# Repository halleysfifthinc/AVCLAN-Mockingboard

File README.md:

# AVCLAN Mockingboard

This project adds an aux in to the stock head unit of compatible Toyota vehicles by emulating an external CD changer. The Mockingboard communicates with the head unit over the AVC-LAN bus, Toyota's name for their messaging protocol over the NEC (now Renesas) IEBus. Also included is a Wireshark dissector for IEBus and AVC-LAN. AVC-LAN is sparsely documented publicly; this dissector collects what's known from prior art alongside my own findings.

# Features:

- Select/switch between internal CD player and mockingboard by pressing the "CD" button (repeated presses toggle between internal and external CD players)
- Generally complete handling of physical interface (track next/prev, fast-forward/rewind, track/disk repeat and random; "scan" button and change disc buttons are currently unimplemented for lack of use/purpose)
- Play/pause, next/prev control of connected phones via headset functions (mimicing the button press on a wired headset; requires phone support and connection using a TRRS aux cable)

## Future plans (Mockingboard v2)

- Bluetooth functionality
  - "Scan" button repurposed to enter bluetooth pairing mode
  - Button actions (play/pause, track skip, ff/rw, \[disc\] repeat/shuffle) mapped to AVRCP
  - Song info/status (time, etc) relayed to head-unit (i.e. time display matches actual song/audio time)
- Redesigned hardware based on RPi Pico 2W (RP2350 + Bluetooth)
  - PIO used to implement:
    - AVCLAN comms
    - I2S audio
  - Dual audio input options (aux in, bluetooth)
    - Switched audio jack to sense aux plug presence
  - Audio codec with differential output (better rejection of electrical noise, e.g. from adjacent AVCLAN bus lines)
  - Switching regulator (easier assembly)
  - CAN transceiver
    - TX/RX connected to different diodes (or different pads of a single dual/multicolor LED package) for observability

# Helpful links/prior art:

- IEBus/AVCLAN decoder and message dumps (inc. a CD changer) for Sigrok
    - https://github.com/sigrokproject/sigrok-test/pull/22
    - https://github.com/sigrokproject/sigrok-dumps/pull/43
    - https://github.com/sigrokproject/libsigrokdecode/pull/106
- https://web.archive.org/web/20230319000356/http://softservice.com.pl/corolla/avc/avclan.php
- https://web.archive.org/web/20040617005106/http://www.interfacebus.com/Design_Connector_IEbus.html
- https://web.archive.org/web/2/https://old.pinouts.ru/Car-Stereo-Toyota-Lexus/Toyota_1990-2002_CD_Chang_pinout.shtml
- https://web.archive.org/web/20240519043021/https://pop.fsck.pl/hardware/toyota-corolla.html
- https://github.com/GadgetNutt/AVC-LAN-Module-Builder

# Firmware

### Building

#### With VS Code:

1. Install VS Code and Docker
    - Required extensions: Dev Containers
2. Open repo in VS code and wait for notification asking to re-open in dev container.
    - Wait for container to build and extensions to install
3. Select CMake build configuration
4. Start developing!

#### Natively/without VS Code Dev Containers
1. Install avr-gcc >= v13.1, binutils >= v2.39, cmake >= v3.24
2. Configure cmake with a hardware-target preset, `cmake --list-presets` to discover options
    - Trigger builds with e.g. `cmake --build out/build/attiny3216`
3. Start developing!

# Hardware

## First generation

See [here](hardware/mockingboard-v1/README.md) for details.

## Second generation

Under development!

# Protocol reverse-engineering

The "scripts/packet-analysis" folder contains a [Wireshark](https://www.wireshark.org/) [Lua plugin](https://www.wireshark.org/docs/wsdg_html_chunked/wsluarm.html) that defines a dissector for IEBUS and AVC-LAN messages.

The dissector's `known_devices` / `known_actions` tables are the source of truth
for AVC-LAN device and action names. `scripts/sync_avclan_enums.py` reconciles
the firmware's C++ `Device` / `Action` enums (and every reference under `src/`)
against them, matching by value so renamed values are propagated. It runs as a
pre-commit hook — the top-level CMake configure step points `core.hooksPath` at
`.githooks/`, so `cmake --preset …` activates it automatically (opt out with
`-DINSTALL_GIT_HOOKS=OFF`; `git commit --no-verify` bypasses one commit). The
hook only reports drift; run `scripts/sync_avclan_enums.py --fix` to apply, and
`--lint` to check that the dissector's own names are valid identifiers.

# License

The firmware for this project is licensed under the [GNU GPLv3](https://www.gnu.org/licenses/gpl-3.0.html). The AVR-Attiny3216 hardware target depends on a vendored [MIT](https://spdx.org/licenses/MIT) licensed [UART library](https://github.com/jnk0le/AVR-UART-lib), and the [MPL-2.0](https://www.mozilla.org/MPL/2.0/) licensed [avr-libstdcpp](https://github.com/modm-io/avr-libstdcpp/) C++ STL subset.
The hardware is licensed under the [Solderpad Hardware License v2.1](http://solderpad.org/licenses/SHL-2.1/), a
wraparound license to the [Apache License 2.0](https://apache.org/licenses/LICENSE-2.0.txt).

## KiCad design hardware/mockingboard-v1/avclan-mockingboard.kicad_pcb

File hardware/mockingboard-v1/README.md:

# Hardware

I ordered the boards partially assembled from JLCPCB (to keep costs down, I ordered and soldered some non-standard/stocked parts myself.)

The non-populated/assembled BOM is:

| Mouser #:           | Mfr. #:          | Desc.:                                                                                                       | Order Qty. | Unit Price (USD) |
| ------------------- | ---------------- | ------------------------------------------------------------------------------------------------------------ | ---------- | ----------- |
| 579-ATTINY3216-SNR  | ATTINY3216-SNR   | 8-bit Microcontrollers - MCU 8-bit Microcontrollers - MCU 20MHz, 32KB, SOIC20, Ind 105C, Green, T&R          | 1          | $1.27       |
| 523-L717SDE09PA4CH4 | L717SDE09PA4CH4F | D-Sub Standard Connectors D-Sub Standard Connectors D SUB R/A                                                | 1          | $1.98       |
| 490-SJ-43514        | SJ-43514         | Phone Connectors Phone Connectors audio jack, 3.5 mm, rt, 4 conductor, through hole, 0 switches              | 1          | $1.35       |
| 667-ERZ-V20D220     | ERZ-V20D220      | Varistors Varistors 22V 2000A ZNR SUR ABSORBER 20MM                                                          | 1          | $1.24       |
| 538-22-28-8093      | 22-28-8093       | Headers & Wire Housings Headers & Wire Housings 2.54MM BREAKAWAY RA 9 CKT Gold                               | 2          | $0.76       |
| 865-XC6701D502JR-G  | XC6701D502JR-G   | LDO Voltage Regulators LDO Voltage Regulators 28V High Speed Voltage Regulator                               | 1          | $1.36       |
| 563-EXN-23350-BK    | EXN-23350-BK     | Enclosures, Boxes, & Cases Enclosures, Boxes, & Cases Extruded Aluminum Enclosure Black (1.4 X 2.7 X 1.9 In) | 1          | $14.40      |

An earlier version of the board* lacked cutouts in the corners to fit the ends of the intended housing, so I haven't used the listed enclosure (yet).

*Only version of the board I have ordered so far.

### Flashing

The CMake target `flash` uses the AVRDude utility using the "serialupdi" programmer type. I use a [USB => Serial converter](https://www.adafruit.com/product/5335) with the Rx and Tx lines connected, using one of the options described [by SpenceKonde here](https://github.com/SpenceKonde/AVR-Guidance/blob/master/UPDI/jtag2updi.md).

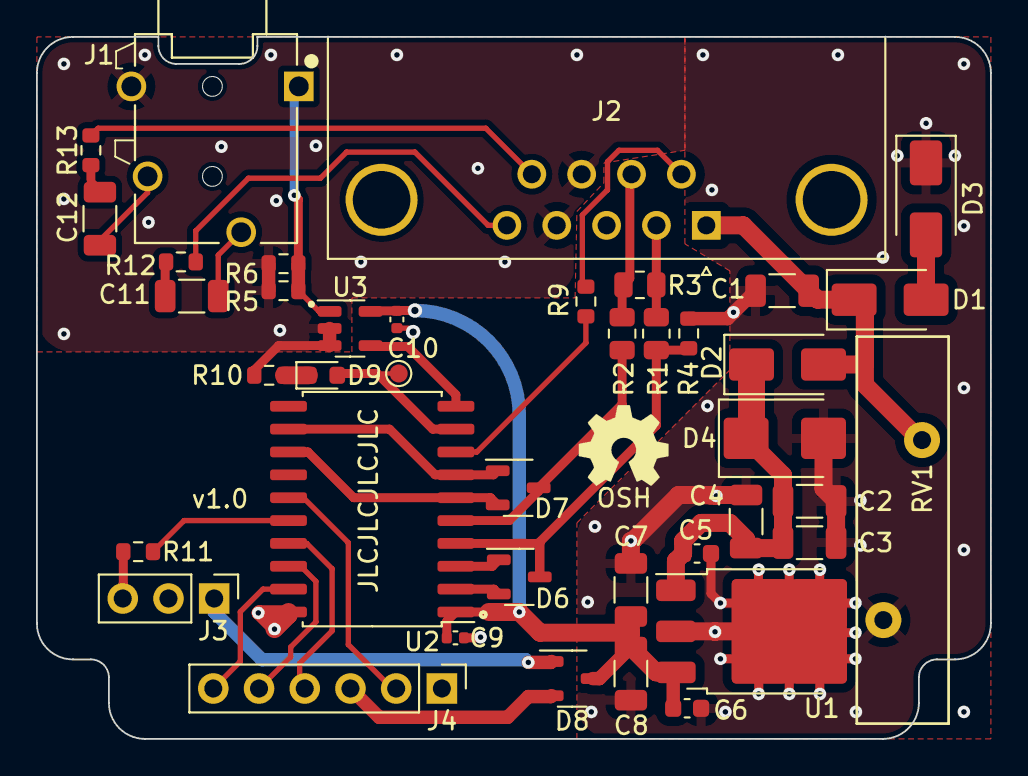
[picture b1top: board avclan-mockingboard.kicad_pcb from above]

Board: 4 copper layers, 53.0 x 39.0 mm, 40 parts (0 on the bottom side), 33 nets.

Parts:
C1: 1n 100V; C_1206_3216Metric
C2, C3, C4: 10u 50V; C_1206_3216Metric
C5, C6: 1u 50V; C_0603_1608Metric
C7, C8, C11, C12: 47u 10V; C_1206_3216Metric
C9, C10: 4u7; C_0402_1005Metric
D1, D2: SS210; D_SMA
D3: 1SMAF4742A; D_SMA
D4: SM6T15A; D_SMB
D6, D8: BAT54C,215; SOT-23-3
D7: BAT54A,215; SOT-23-3
D9: KT-0603R; LED_0603_1608Metric
J1: Audio In; CUI_SJ-43514
J2: DB9; DSUB-9_Male_Horizontal_P2.77x2.84mm_EdgePinOffset7.70mm_Hou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
J3: Conn_01x03; PinHeader_1x03_P2.54mm_Vertical
J4: Conn_01x06; PinHeader_1x06_P2.54mm_Vertical
R1, R2: 180; R_0805_2012Metric
R3: 120; R_0805_2012Metric
R4, R5, R6, R9: 10k; R_0603_1608Metric
R10, R11: 470; R_0603_1608Metric
R12, R13: 15; R_0603_1608Metric
RV1: ERZ-V20D220; RV_Disc_D21.5mm_W5.1mm_P10mm
TP1: TestPoint; TestPoint_Pad_D1.0mm
U1: XC6701D502JR-G; TO-252-3_TabPin2
U2: ATtiny3216; SOIC-20W_7.5x12.8mm_P1.27mm
U3: 74LVC1G66; SOT-23-5

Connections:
+5V: C6.1, C7.1, C8.1, C9.1, C10.1, D8.3 (K), U1.3 (Vout), U2.1 (VCC), U3.5 (VCC)
+12V: C1.1, D1.1 (K), D2.2 (A), J2.1 (BAT), RV1.1
/12V_CLEAN: C2.1, C3.1, C4.1, C5.1, D2.1 (K), D4.1 (A1), U1.1 (Vin)
/AC2 OUT: D9.2 (A), TP1.1, U2.9 (PB2)
/AUDIO-L: J2.9 (R-), R13.1
/AUDIO-R: J2.5 (GND), R12.2
AUDIO_L: C12.1, J1.2 (T)
AUDIO_R: C11.1, J1.3 (R1)
AVCLAN_BUS_TX+: J2.2 (BUS+), R1.2, R3.2
AVCLAN_BUS_TX-: J2.7 (BUS-), R2.2, R3.1
AVCLAN_TX+: D6.3 (A), R1.1, R4.1, U2.4 (PA6)
AVCLAN_TX-: D7.3 (A), R2.1, U2.5 (PA7)
CTS: J4.2, U2.15 (PC3)
GND: C1.2, C2.2, C3.2, C4.2, C5.2, C6.2, C7.2, C8.2, C9.2, C10.2, D3.1 (K), D4.2 (A2), J1.4 (R2), J2.3 (L+), J2.4 (R+), J2.8 (L-), J3.2, J4.1, R4.2, R5.2, R6.2, R10.2, RV1.2, U1.2 (GND), U2.20 (GND), U3.2, U3.3 (GND)
MIC_CONTROL: U2.10 (PB1), U3.4
MUTE: R9.1, U2.8 (PB3)
unnamed: C11.2, R12.1
unnamed: C12.2, R13.2
unnamed: D1.2 (A), D3.2 (A)
unnamed: D9.1 (K), R10.1
unnamed: J1.1 (S), R5.1, R6.1, U3.1
unnamed: J2.6 (IGN/ACC), R9.2
unnamed: J3.3, R11.2
RTS: J4.6, U2.19 (PA3)
RxD: J4.4, U2.18 (PA2)
SERIAL_PWR: D8.2 (K), J4.3
TxD: J4.5, U2.17 (PA1)
UPDI: R11.1, U2.16 (~RESET/PA0)
UPDI_PWR: D8.1 (A), J3.1
WOA: D6.2 (K), U2.2 (PA4)
WOB: D6.1 (K), U2.3 (PA5)
WOC: D7.1 (K), U2.7 (PB4), U2.12 (PC0)
WOD: D7.2 (K), U2.6 (PB5), U2.13 (PC1)

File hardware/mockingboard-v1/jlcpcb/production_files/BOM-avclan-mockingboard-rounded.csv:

Comment,Designator,Footprint,LCSC
SM6T15A,D4,D_SMB,C118275
"BAT54A,215",D7,SOT-23-3,C130910
10u 50V,"C2,C3,C4",C_1206_3216Metric,C13585
SS210,"D1,D2",D_SMA,C14996
1u 50V,"C5,C6",C_0603_1608Metric,C15849
10k,"R4,R5,R6,R7,R8,R9",R_0603_1608Metric,C17414
120,R3,R_0805_2012Metric,C17437
15,"R12,R13",R_0603_1608Metric,C22810
KT-0603R,D9,LED_0603_1608Metric,C2286
470,"R10,R11",R_0603_1608Metric,C23179
4u7,"C10,C9",C_0402_1005Metric,C23733
180,"R1,R2",R_0805_2012Metric,C25270
1SMAF4742A,D3,D_SMA,C3013762
"BAT54C,215","D6,D8",SOT-23-3,C37704
74LVC1G66,U3,SOT-23-5,C5375974
3V3,D10,D_MiniMELF,C8056
1n 100V,C1,C_1206_3216Metric,C9196
47u 10V,"C11,C12,C7,C8",C_1206_3216Metric,C96123

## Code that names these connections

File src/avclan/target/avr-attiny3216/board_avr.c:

// copyright (C) 2006 Marcin Slonicki <marcin@softservice.com.pl>
// copyright (C) 2007 Louis Frigon
// Copyright (C) 2015 Allen Hill <allenofthehills@gmail.com>
// SPDX-License-Identifier: GPL-3.0-or-later

// ATtiny3216 board bring-up: main-clock prescaler + GPIO config for pins not
// owned by a peripheral's own init.

#include <avr/interrupt.h>
#include <avr/io.h>
#include <avr/xmega.h> // _PROTECTED_WRITE

#include "hal/board.h"

void board_init(void) {
  // Main clock prescale (CLK_PRESCALE / CLK_PRESCALE_DIV come from the build).
  _PROTECTED_WRITE(CLKCTRL.MCLKCTRLB, (CLK_PRESCALE | CLK_PRESCALE_DIV));

  // Set pins PC2-3, PB0,3-5 as inputs
  PORTC.DIRCLR = (PIN2_bm | // Unconnected
                  PIN3_bm); // CTS
  PORTB.DIRCLR = (PIN0_bm | // Unconnected
                  PIN3_bm | // IGN_SENSE
                  PIN4_bm | // Unused, but connected to WOC (PC0)
                  PIN5_bm); // Unused, but connected to WOD (PC1)

  // Enable pull-up resistor and disable input buffer (reduces any EM caused
  // pin toggling and saves power) for unused and unconnected pins
  PORTC.PIN2CTRL = PORT_PULLUPEN_bm | PORT_ISC_INPUT_DISABLE_gc;
  PORTB.PIN0CTRL = PORT_PULLUPEN_bm | PORT_ISC_INPUT_DISABLE_gc;

  // TODO: Remove once IGN_SENSE hardware is fixed
  PORTB.DIRSET = PIN3_bm;
  PORTB.OUTSET = PIN3_bm;

  // Output only pins: PA3-5, PB1-2,4-5; PC0-1
  // TODO: TxD (PA1), RTS (PA3) is output only, test if RxD needs the input
  // buffer or if the UART peripheral bypasses it
  PORTA.PIN3CTRL = PORT_ISC_INPUT_DISABLE_gc; // RTS
  PORTA.PIN4CTRL = PORT_ISC_INPUT_DISABLE_gc; // WOA
  PORTA.PIN5CTRL = PORT_ISC_INPUT_DISABLE_gc; // WOB
  PORTB.PIN1CTRL = PORT_ISC_INPUT_DISABLE_gc; // MIC_CONTROL
  PORTB.PIN4CTRL = PORT_ISC_INPUT_DISABLE_gc; // non-driving WOC
  PORTB.PIN5CTRL = PORT_ISC_INPUT_DISABLE_gc; // non-driving WOD
  PORTC.PIN0CTRL = PORT_ISC_INPUT_DISABLE_gc; // WOC
  PORTC.PIN1CTRL = PORT_ISC_INPUT_DISABLE_gc; // WOD
}

void board_enable_interrupts(void) { sei(); }

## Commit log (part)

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2015-07-20 Branch update
2015-07-23 Merged Marcin's AVC-LAN driver
2015-07-23 Updated Makefile for new driver/main file
2015-07-24 Compile/linking required changes
2015-07-24 Removed old schematics
2015-07-24 Removed old files
2015-07-27 Message read now works
2015-07-27 Added avr-size rule
2015-07-28 Data visuals/research
2023-07-16 Uncommitted changes from 8 years ago
2023-08-03 Replace Timer1 with periodic interrupt timer from the RTC
2023-08-03 Update to use attiny1616 AC2 and TCB1
    - Change AVC output enable/disable to only change input/output of pin 7;
    only one pin should need to be used to send (i.e. actual differential
    signaling isn't being used, therefore, we can achieve the necessary
    (single-ended) differential voltage using only one pin, leaving the
    other outputting low)
    - Use virtual ports to enable setting output status with single
2023-08-07 Update serial registers
2023-08-07 Rename HexInc -> incBCD; comment out unused decrement functions
2023-08-17 File cleaning
2023-08-20 Reformat using clang format
2023-08-20 Remove LED functionality
2023-08-20 Fix compiler complaint about VPORTA_OUT in asm
2023-08-20 Update makefile
2023-08-20 Add vscode settings
2023-08-20 Remove old/irrelevant files
2023-08-20 Switch PROGMEM related uses to regular flash (flat address space in avrxmega3)
2023-08-20 Indent case labels
2023-08-21 Use alternate UART TxD/RxD pins
2023-08-21 Replace byte/word typedefs with uintN_t
2023-08-21 Fix warning about array subscript [0] outside array bounds
2023-08-21 Move source files into `src` dir
2023-08-22 Switch to CMake
2023-08-22 Setup Dev Containers for VS Code (easy toolchain/build setup)
2023-08-22 Adjust for difference between GNU avr-libc IO headers and Atmel IO headers
2023-08-22 Only download Microchip pack if avr-libc doesnt support ATtiny3216
2023-08-22 Reformat comments
2023-08-23 Configure unused and/or output only pins
2023-08-23 Change split 12bit variables to single uint16_t vars
2023-08-23 Enable AC2_OUT for LED
2023-08-23 Replace a bunch of defines with an enum
2023-08-23 Change parity_bit from global to local for read/send functions
2023-08-25 Remove unused variables
2023-08-27 Add generic dispatch for AVCLAN_sendbits; simplifies calling use for 12 bit words
2023-08-29 Exclude build artifacts from C/C++ extension analysis
2023-08-29 Refactor send/receive functions to use a new `AVCLAN_frame_t` type
2023-09-01 Remove non-functional variables
2023-09-03 More cleanly separate specific functionality into the relevant files
2023-09-03 More reorganization [nfc]
2023-09-03 Tooling updates and modification suggested by clang-tidy
2023-09-03 Switch master/slave replacements to OSHWA recommended controller/peripheral
2023-09-03 Update LICENSE and notices in files
2023-09-03 Remove unnecessary extern specifier for functions
2023-09-03 Sort clang-tidy options
2023-09-03 Add copyright attribution for louis frigon too
2023-09-03 Add compiler explorer extension for optimizing functions
2023-09-03 Annotate cases
2023-09-03 Remove unused functions
2023-09-03 Move incBCD to sniffer; only used there
2023-09-03 Copy settings to devcontainer
2023-09-03 Add RelWithDebInfo build preset
2023-09-03 Change sendbit timer config to optimize function length (insns)
2023-09-03 Rename send/read bits/bytes functions and rearrange
2023-09-04 Re-add an AVCLAN summary/diagram
2023-09-10 Implement bit-read timing with TCB0 pulse-width measurement
2023-09-10 Setup timing better (fuses, clock speed, TCB clock speed)
2023-09-10 Setup and bugfix programming with avrdude
2023-09-10 Remove makefile; use CMake instead
2023-09-10 Update/fix pin levels for new transmission design
2023-09-10 Refine timing calculations; use for serial baudrate calculation
2023-09-12 Update signal measuring and apply new measurements to bit-timings
2023-09-12 Add printhex12 function
2023-09-12 Add toggleable verbose debugging messages and tweak/improve the serial interface
2023-09-12 Remove erroneous PUBLIC include_directory
2023-09-13 Update AVCLAN summary
2023-09-13 Fix reading functions
2023-09-14 Rename INPUT_IS_SET/CLEAR to BUS_IS_IDLE
2023-09-14 Change serial baud to 500k at double-speed; but add cmake option for serial rxmode
2023-09-14 More send related bugfixes
2023-09-15 Rearrange some functions
2023-09-15 Add binary printing and reading/parsing from serial
2023-09-16 Fix UART 2x speed config
2023-09-16 Fix printBinary flag
2023-09-17 Tweak formatting rules
2023-09-17 Add @jnk0le AVR-UART-lib master
2023-09-17 Apply formatting rules [nfc]
2023-09-17 Fix bad reformats
2023-09-17 Initial adaptations for avrxmega3
2023-10-09 Fix remaining build issues and reformat comments in usart_config
2023-10-09 Move readkey var to sniffer
2023-10-09 Fix Event being sent when cd_mode isnt stPlay
2023-10-16 Fix binary printframe
2023-10-23 Remove copy of libc function
2023-10-24 Move RTC PIT to avclandrv and add CD status struct and answerreq
2023-10-24 Remove hardcoded length in favor of const evaled sizeof
2023-10-25 Add muteing functionality and avoid unnecessary work when muted
2023-10-25 Remove non-functioning variable
2023-10-25 Rename `for_me` to `shouldACK`
2023-10-25 [NFC] Update comments and move a defines
2023-10-26 Reorder avclan functions and rename `AVCLAN_SendAnswer` to `AVCLAN_respond`
2023-10-26 Remove bad send init commands function
2023-10-28 Boost UART speed
2023-10-28 Rename HU/CD_ID and change to defines (never need to change at runtime)
2023-10-28 Optimize binary printframe (reduce number of RS232_print calls)
2023-10-28 Refactor frame handling and response code
2024-08-23 Add Wireshark packet dissector plugin and associated tools
2024-08-23 Add circuit board and wiring harness
2024-08-23 Update devcontainer
2024-08-23 Update Cmakelists
2024-08-23 Commit old working changes
2024-08-23 Add README
2024-10-08 Add copyright year/author
2024-10-08 Remove mistakenly committed file
2024-10-08 Ignore more files
2025-10-09 Expand Wireshark packet dissector support
2025-10-09 Improve action/function names and tweak report responses
2025-10-10 Add normalized brightness value to packet dissection
2026-05-04 Update pcap setup
2026-05-04 Replace use of numeric literals with appropriate enums
2026-05-04 Convert some local macros to inline functions
2026-05-05 Refactor message handling switch tree
2026-05-05 Recognize more actions
2026-05-05 Refactor canned message setting
2026-05-05 Combine similar sendbit functions
2026-05-05 Refactor error handling in read/send frame
2026-05-06 Add some compiler warnings and fix revealed bugs
2026-05-06 Refactor AVCLAN_parseframe call signature to avoid dynamic allocs
2026-05-06 Fix incorrect time updating logic
2026-05-06 fixup readframe error logs
2026-05-08 Substantially refactor ~everything to separate concerns and improve flow clarity
    Highlights:
    - Remove all use of malloc and friends
    - Refactor message handling functions to work with references
    - Move core message read => triage => respond logic loop to main
    function
    - Improve message triage and support follow-up messages
2026-05-08 Cleanup flag setting cases
2026-05-08 Fix memory leaks from refactor
2026-05-11 Reorder error enums for simpler partial success check
2026-05-11 store the results of `tmp & 1` to avoid recalc
2026-05-11 Fix incorrect address-of (and rename argument resp => out)
2026-05-11 Fix bad function call
2026-05-12 Group pointer increments for better assembly (in recent GCC)
2026-05-14 Reduce variable scope (global => local; reduce local var scope size)
2026-05-14 Fix incorrect definition/initialization of caches
2026-05-14 Improve error messaging/handling
2026-05-14 Add QoL correctness checks (not strictly necessary but behaves better)
2026-05-14 Specify enum size to drop (potentially surprising) enum size compile flag
2026-05-16 Manually inline sbi/cbi macros
2026-05-16 Fix binary msg read edge cases
2026-05-16 Make global message templates static const
2026-05-16 Use bool consistently now that we're on C23
2026-05-16 Tighten PIT interrupt and avoid some BCD edge-cases
2026-05-16 Mark incrementRead as static inline
2026-05-16 Flatten msg triage switches to dispatch on first 3 bytes together (as uint32_t)
2026-05-16 Minor reorg of cmakelists
2026-05-16 Fix missed REPL docs update
2026-05-16 Rename field broadcast => is_unicast
    Improves readability and logical flow clarity
2026-05-16 Use ATOMIC_BLOCK instead of manual cli/sei
2026-05-16 Use better name for variable
2026-05-16 Replace iffy bitfield use with uin8_t fields and enums
2026-05-16 Prevent pushing nullptr into queues
2026-05-16 Remove unused enum
2026-05-16 Archive old files
2026-05-16 Add some missing volatile annotations
2026-05-16 Use more readable byte access patterns (compiles the same)
2026-05-16 chown usb device after creating container
2026-05-16 fix: V-001 security vulnerability
    Automated security fix generated by Orbis Security AI
2026-06-12 update dissector
2026-06-12 Refactor cmake/presets for easier serial usb device selection
2026-06-13 more dissector improvements
2026-06-13 Shift state machine from main loop to driver file
2026-06-13 Fix some safety/ergonomic issues
2026-06-13 Tweak/fix(?) Initial/Playback/Loading responses
2026-06-15 Fix track change logic (track is/should be serialized as BCD)
2026-06-15 Fix mutebus and improve bool literal hygiene
2026-06-19 Add headset function control
2026-06-19 add more static annotations
2026-06-19 update ignores
2026-06-19 PIT shouldnt start off enabled
2026-06-19 reduce scope/improve locality of response arrays
2026-06-19 Improve periodic status reporting (tune interval better, reset count when changing time)
2026-06-19 use direct instead of pointer access for cd track/min/sec
2026-06-19 Stop playing if nobody's listening
2026-06-19 Resolve/unlatch a latched comparator
2026-06-19 reorg some functionality
2026-06-19 Correctly respond to button actions (CMD_SW state report)
2026-06-19 Delay starting status timer until state has been normalized
2026-06-19 start/stopEvent bodies should be in atomic blocks
2026-06-19 Improve/correct several response bodies
2026-06-19 Support fast-forward/rewind
2026-06-19 Only "stop playing" if we ARE playing
2026-06-21 Only play (headset) on after first pause
2026-06-21 Stop "playing" after 2 failed status updates
2026-06-21 Tweak debug play/pause test
2026-06-21 Properly fix headset functions when there's bus activity
2026-06-21 Add triple-press for skip back
2026-06-22 reorg hardware folder for v2 dev
2026-06-23 Update devcontainer startup to consistently chown passed-thru usb devices
2026-06-24 Decouple hardware specific code from generic, agnostic code
2026-06-24 Update copyright headers to use SPDX id's
2026-06-24 use out/build for preset build directory
2026-06-24 Prep for C++ port
2026-06-25 Port Queue to C++
    Some knock-on changes to keep a simple design:
    - Bake the data array into AVCLAN_frame_t
    - Bundle the response/reaction with AVCLAN_frame_t
    - (Needed to maintain correct/simple ownership semantics with the
    cache and outgoing/incoming queues)
    - Switch status frame update ticks to use a regular
2026-06-26 Add C++ `Peripheral` class
2026-06-26 fix some clang-tidy warnings
2026-06-26 Add C++ `Bus` class for the physical layer interface
2026-06-27 Parameterise `Peripheral` by its `Device`s and add `CDChanger` as one
